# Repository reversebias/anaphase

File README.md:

# anaphase wireless split keyboard

anaphase is a Bluetooth/USB split ergonomic keyboard with a 3D printed case and custom PCB base.

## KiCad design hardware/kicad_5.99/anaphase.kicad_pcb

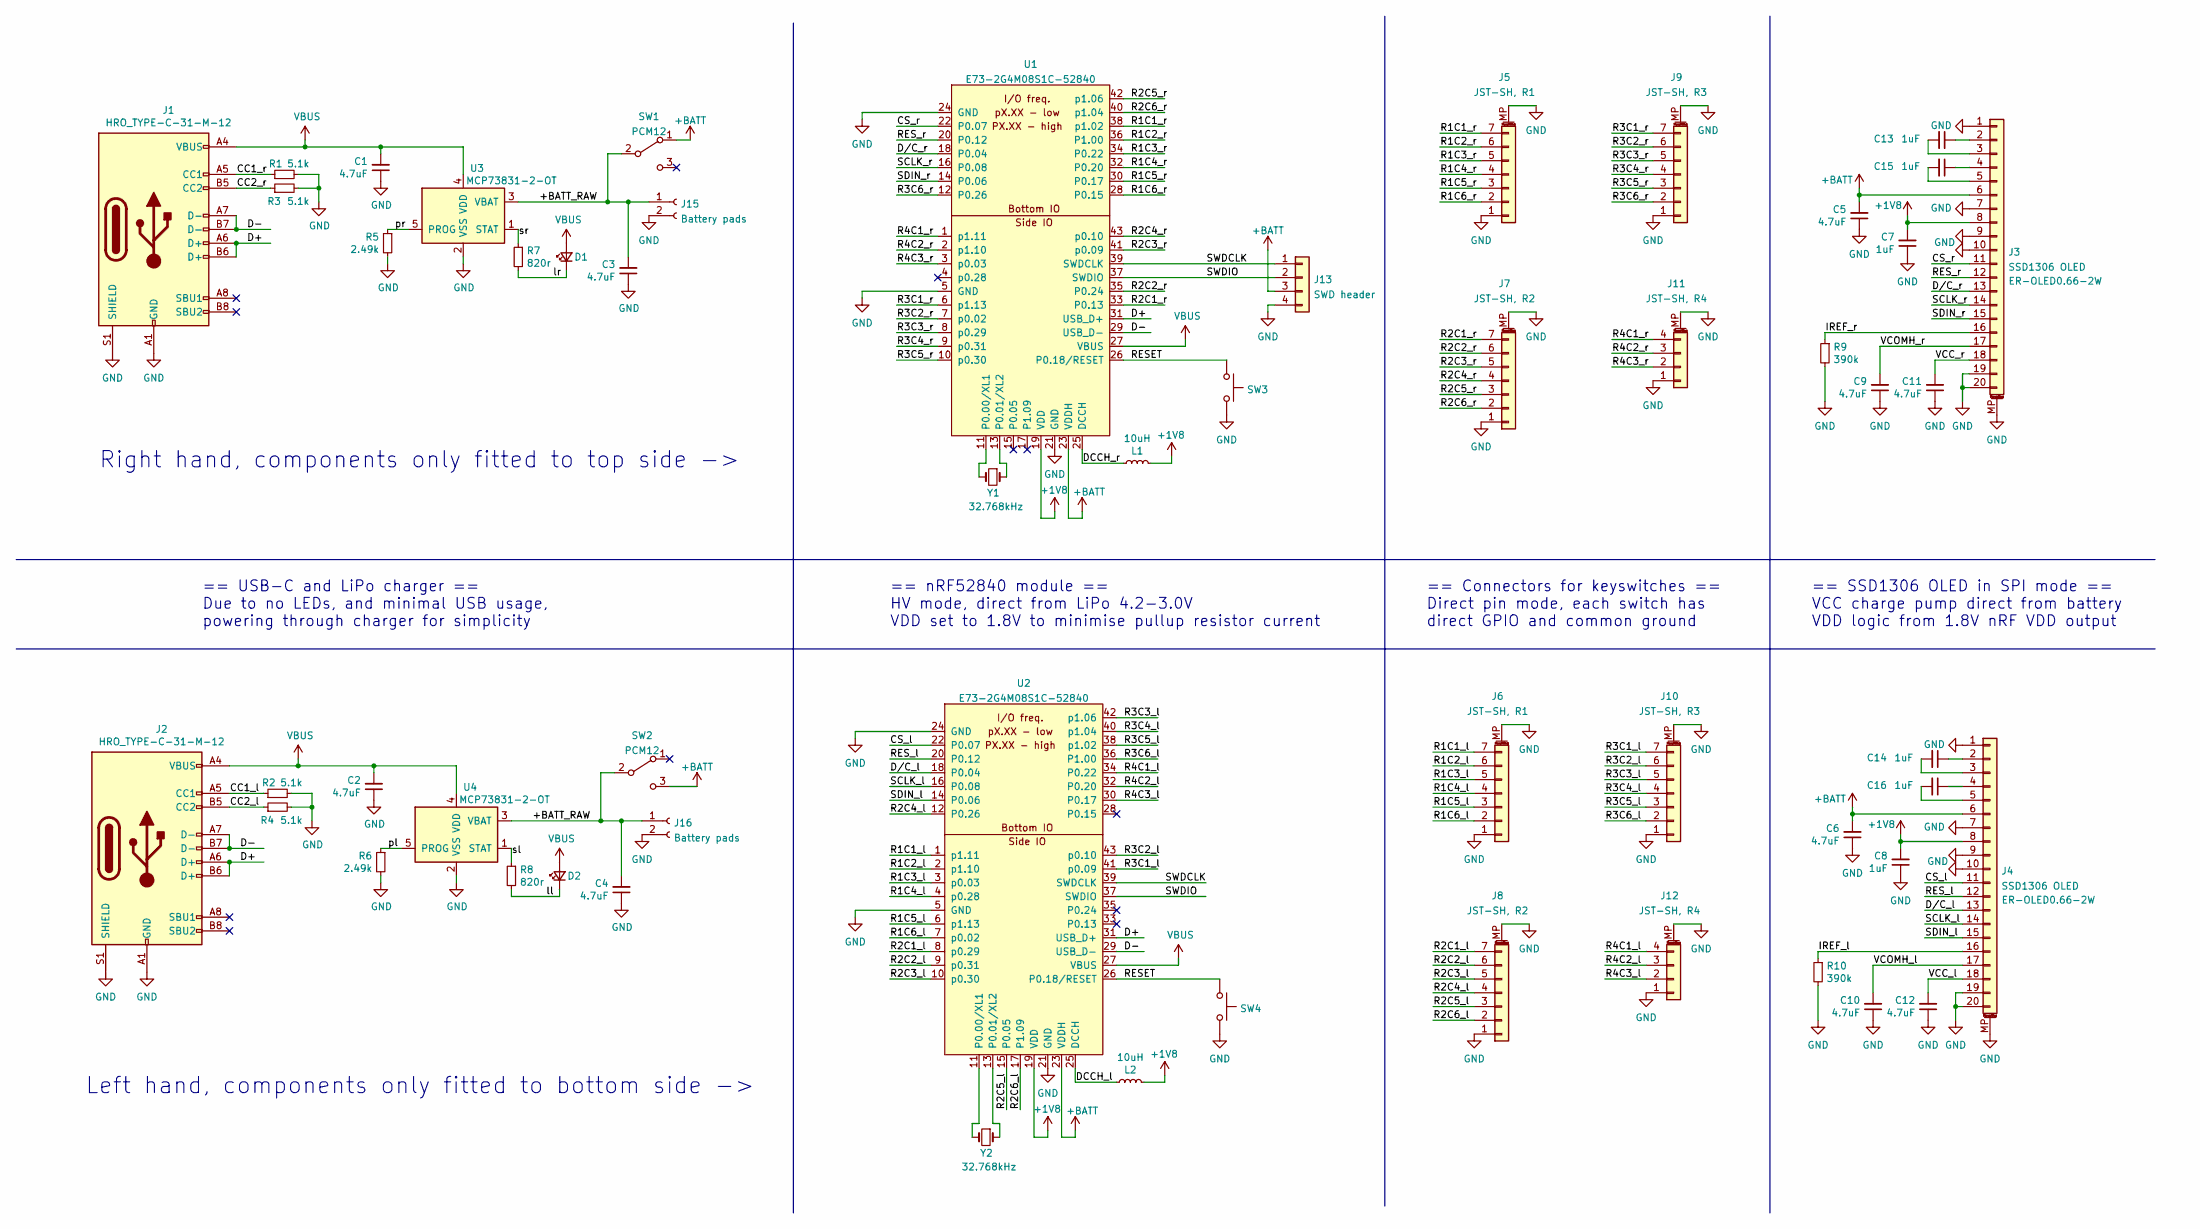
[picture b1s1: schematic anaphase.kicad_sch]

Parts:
C1, C2, C3, C4, C5, C6, C9, C10, C11, C12: 4.7uF; C_0603_1608Metric_Pad1.08x0.95mm_HandSolder
C7, C8, C13, C14, C15, C16: 1uF; C_0603_1608Metric_Pad1.08x0.95mm_HandSolder
D1, D2: AMBER; LED_0603_1608Metric
J1, J2: HRO_TYPE-C-31-M-12; USB_C_Receptacle_HRO_TYPE-C-31-M-12
J3, J4: SSD1306 OLED; Molex_5052782033
J5, J6: JST-SH, R1; JST_SH_BM07B-SRSS-TB_1x07-1MP_P1.00mm_Vertical
J7, J8: JST-SH, R2; JST_SH_BM07B-SRSS-TB_1x07-1MP_P1.00mm_Vertical
J9, J10: JST-SH, R3; JST_SH_BM07B-SRSS-TB_1x07-1MP_P1.00mm_Vertical
J11, J12: JST-SH, R4; JST_SH_BM04B-SRSS-TB_1x04-1MP_P1.00mm_Vertical
J13: SWD header; PinHeader_1x04_P2.54mm_Vertical
J15, J16: Battery pads; L_1210_3225Metric
L1, L2: 10uH; L_0603_1608Metric_Pad1.05x0.95mm_HandSolder
R1, R2, R3, R4: 5.1k; R_0603_1608Metric_Pad0.98x0.95mm_HandSolder
R5, R6: 2.49k; R_0603_1608Metric_Pad0.98x0.95mm_HandSolder
R7, R8: 820r; R_0603_1608Metric_Pad0.98x0.95mm_HandSolder
R9, R10: 390k; R_0603_1608Metric_Pad0.98x0.95mm_HandSolder
SW1, SW2: PCM12; SW_SPDT_PCM12
SW3, SW4: SW_Push; SW_Push_SPST_NO_Alps_SKRK
U1, U2: E73-2G4M08S1C-52840
U3, U4: MCP73831-2-OT; SOT-23-5
Y1, Y2: 32.768kHz; Crystal_SMD_MicroCrystal_CM9V-T1A-2Pin_1.6x1.0mm

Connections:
+1V8: C7.2, C8.2, J3.8, J4.8, L1.2, L2.2, U1.19 (VDD), U2.19 (VDD)
+BATT: C5.2, C6.2, J3.6, J4.6, J13.3, SW1.1 (A), SW2.3 (C), U1.23 (VDDH), U2.23 (VDDH)
/+BATT_RAW: C3.2, C4.2, J15.1, J16.1, SW1.2 (B), SW2.2 (B), U3.3 (VBAT), U4.3 (VBAT)
/CC1_l: J2.A5 (CC1), R2.1
/CC1_r: J1.A5 (CC1), R1.1
/CC2_l: J2.B5 (CC2), R4.1
/CC2_r: J1.B5 (CC2), R3.1
/CS_l: J4.11, U2.22 (P0.07)
/CS_r: J3.11, U1.22 (P0.07)
/D+: J1.A6 (D+), J1.B6 (D+), J2.A6 (D+), J2.B6 (D+), U1.31 (USB_D+), U2.31 (USB_D+)
/D-: J1.A7 (D-), J1.B7 (D-), J2.A7 (D-), J2.B7 (D-), U1.29 (USB_D-), U2.29 (USB_D-)
/DCCH_l: L2.1, U2.25 (DCCH)
/DCCH_r: L1.1, U1.25 (DCCH)
/D/C_l: J4.13, U2.18 (P0.04)
/D/C_r: J3.13, U1.18 (P0.04)
/IREF_l: J4.16, R10.1
/IREF_r: J3.16, R9.1
/R1C1_l: J6.7, U2.1 (p1.11)
/R1C1_r: J5.7, U1.38 (p1.02)
/R1C2_l: J6.6, U2.2 (p1.10)
/R1C2_r: J5.6, U1.36 (P1.00)
/R1C3_l: J6.5, U2.3 (p0.03)
/R1C3_r: J5.5, U1.34 (P0.22)
/R1C4_l: J6.4, U2.4 (p0.28)
/R1C4_r: J5.4, U1.32 (P0.20)
/R1C5_l: J6.3, U2.6 (p1.13)
/R1C5_r: J5.3, U1.30 (P0.17)
/R1C6_l: J6.2, U2.7 (p0.02)
/R1C6_r: J5.2, U1.28 (P0.15)
/R2C1_l: J8.7, U2.8 (p0.29)
/R2C1_r: J7.7, U1.33 (P0.13)
/R2C2_l: J8.6, U2.9 (p0.31)
/R2C2_r: J7.6, U1.35 (P0.24)
/R2C3_l: J8.5, U2.10 (p0.30)
/R2C3_r: J7.5, U1.41 (p0.09)
/R2C4_l: J8.4, U2.12 (P0.26)
/R2C4_r: J7.4, U1.43 (p0.10)
/R2C5_l: J8.3, U2.15 (P0.05)
/R2C5_r: J7.3, U1.42 (p1.06)
/R2C6_l: J8.2, U2.17 (P1.09)
/R2C6_r: J7.2, U1.40 (p1.04)
/R3C1_l: J10.7, U2.41 (p0.09)
/R3C1_r: J9.7, U1.6 (p1.13)
/R3C2_l: J10.6, U2.43 (p0.10)
/R3C2_r: J9.6, U1.7 (p0.02)
/R3C3_l: J10.5, U2.42 (p1.06)
/R3C3_r: J9.5, U1.8 (p0.29)
/R3C4_l: J10.4, U2.40 (p1.04)
/R3C4_r: J9.4, U1.9 (p0.31)
/R3C5_l: J10.3, U2.38 (p1.02)
/R3C5_r: J9.3, U1.10 (p0.30)
/R3C6_l: J10.2, U2.36 (P1.00)
/R3C6_r: J9.2, U1.12 (P0.26)
/R4C1_l: J12.4, U2.34 (P0.22)
/R4C1_r: J11.4, U1.1 (p1.11)
/R4C2_l: J12.3, U2.32 (P0.20)
/R4C2_r: J11.3, U1.2 (p1.10)
/R4C3_l: J12.2, U2.30 (P0.17)
/R4C3_r: J11.2, U1.3 (p0.03)
/RESET: SW3.1, SW4.1, U1.26 (P0.18/RESET), U2.26 (P0.18/RESET)
/RES_l: J4.12, U2.20 (P0.12)
/RES_r: J3.12, U1.20 (P0.12)
/SCLK_l: J4.14, U2.16 (P0.08)
/SCLK_r: J3.14, U1.16 (P0.08)
/SDIN_l: J4.15, U2.14 (P0.06)
/SDIN_r: J3.15, U1.14 (P0.06)
/SWDCLK: J13.1, U1.39 (SWDCLK), U2.39 (SWDCLK)
/SWDIO: J13.2, U1.37 (SWDIO), U2.37 (SWDIO)
/VCC_l: C12.2, J4.18
/VCC_r: C11.2, J3.18
/VCOMH_l: C10.2, J4.17
/VCOMH_r: C9.2, J3.17
/ll: D2.1 (K), R8.2
/lr: D1.1 (K), R7.2
/pl: R6.1, U4.5 (PROG)
/pr: R5.1, U3.5 (PROG)
/sl: R8.1, U4.1 (STAT)
/sr: R7.1, U3.1 (STAT)
GND: C1.1, C2.1, C3.1, C4.1, C5.1, C6.1, C7.1, C8.1, C9.1, C10.1, C11.1, C12.1, J1.A1 (GND), J1.A12 (GND), J1.B1 (GND), J1.B12 (GND), J1.S1 (SHIELD), J2.A1 (GND), J2.A12 (GND), J2.B1 (GND), J2.B12 (GND), J2.S1 (SHIELD), J3.1, J3.7, J3.9, J3.10, J3.19, J3.20, J3.MP (MountPin), J4.1, J4.7, J4.9, J4.10, J4.19, J4.20, J4.MP (MountPin), J5.1, J5.MP (MountPin), J6.1, J6.MP (MountPin), J7.1, J7.MP (MountPin), J8.1, J8.MP (MountPin), J9.1, J9.MP (MountPin), J10.1, J10.MP (MountPin), J11.1, J11.MP (MountPin), J12.1, J12.MP (MountPin), J13.4, J15.2, J16.2, R1.2, R2.2, R3.2, R4.2, R5.2, R6.2, R9.2, R10.2, SW3.2, SW4.2, U1.5 (GND), U1.21 (GND), U1.24 (GND), U2.5 (GND), U2.21 (GND), U2.24 (GND), U3.2 (VSS), U4.2 (VSS)
unnamed: C13.1, J3.2
unnamed: C13.2, J3.3
unnamed: C14.1, J4.2
unnamed: C14.2, J4.3
unnamed: C15.1, J3.4
unnamed: C15.2, J3.5
unnamed: C16.1, J4.4
unnamed: C16.2, J4.5
unnamed: U1.11 (P0.00/XL1), Y1.2
unnamed: U1.13 (P0.01/XL2), Y1.1
unnamed: U2.11 (P0.00/XL1), Y2.2
unnamed: U2.13 (P0.01/XL2), Y2.1
VBUS: C1.2, C2.2, D1.2 (A), D2.2 (A), J1.A4 (VBUS), J1.A9 (VBUS), J1.B4 (VBUS), J1.B9 (VBUS), J2.A4 (VBUS), J2.A9 (VBUS), J2.B4 (VBUS), J2.B9 (VBUS), U1.27 (VBUS), U2.27 (VBUS), U3.4 (VDD), U4.4 (VDD)

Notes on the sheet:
Left hand, components only fitted to bottom side ->
Right hand, components only fitted to top side ->
== USB-C and LiPo charger == Due to no LEDs, and minimal USB usage, powering through charger for simplicity
== nRF52840 module == HV mode, direct from LiPo 4.2-3.0V VDD set to 1.8V to minimise pullup resistor current
== Connectors for keyswitches == Direct pin mode, each switch has direct GPIO and common ground
== SSD1306 OLED in SPI mode == VCC charge pump direct from battery VDD logic from 1.8V nRF VDD output

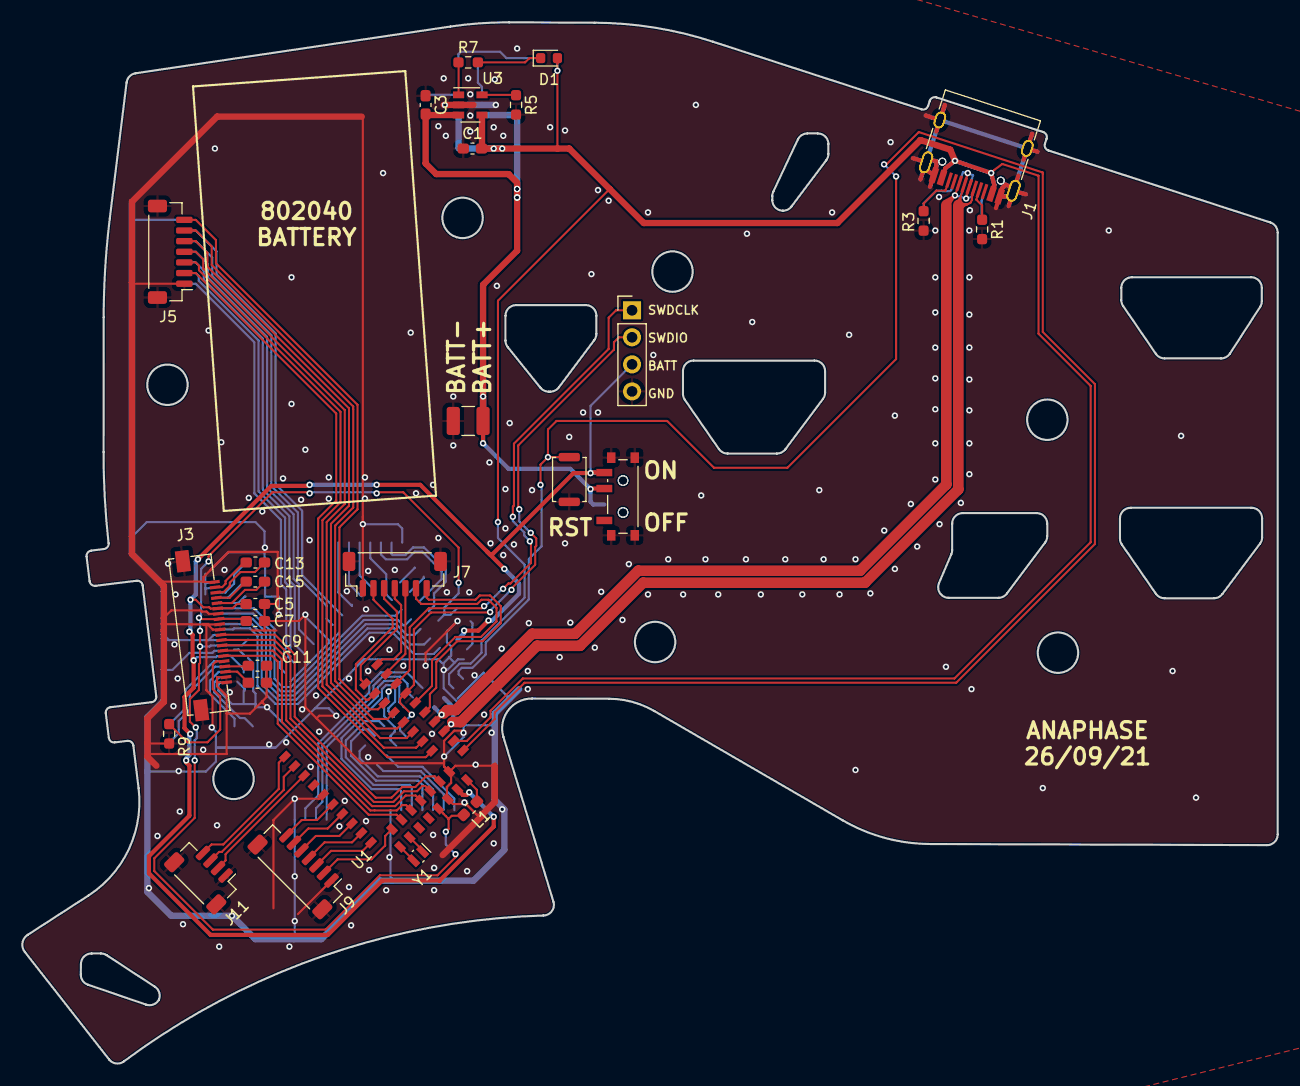
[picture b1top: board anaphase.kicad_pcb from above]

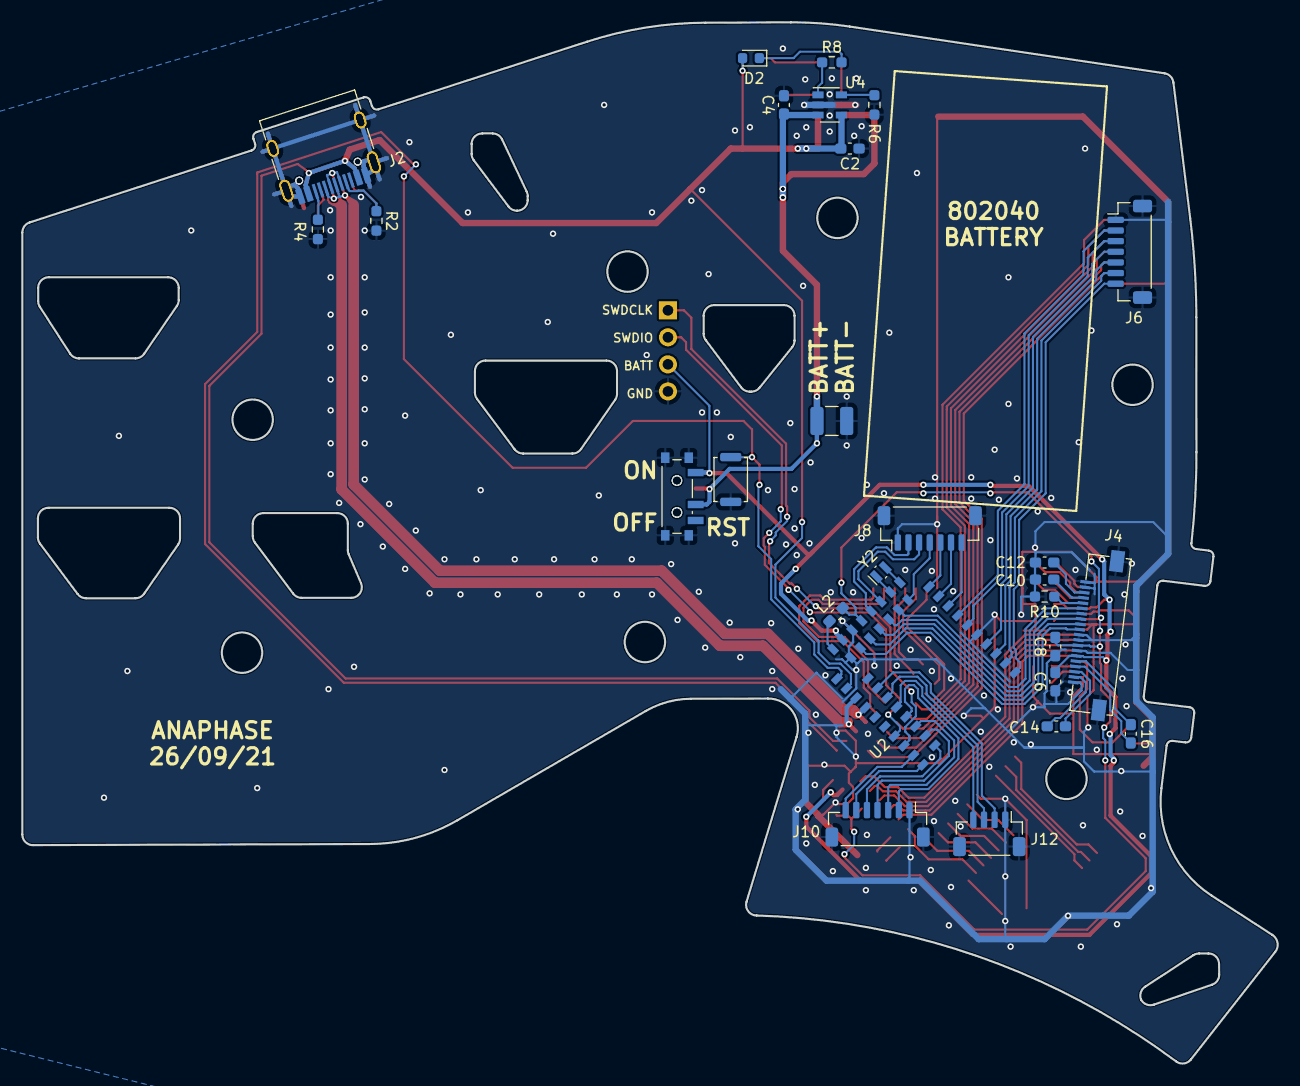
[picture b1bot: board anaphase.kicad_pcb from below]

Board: 2 copper layers, 118.0 x 97.8 mm, 55 parts (27 on the bottom side), 92 nets.

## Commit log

2021-11-01 initial setup of readme
2021-11-01 zmk-config
2021-11-01 non-empty-dir
2021-11-01 numble file structure
2021-11-01 change to split keyboard
2021-11-01 added in fissure files
2021-11-01 new branch for minimal testing
2021-11-01 update for single key
2021-11-01 working spacebar
2021-11-01 oled configured, but no output
2021-11-01 tabs to spaces
2021-11-01 added kconfig
2021-11-01 update based on chat
2021-11-04 working screen, but flipped polarity
2021-11-08 working LCD on single keyboard
2021-11-10 split functionality working
2021-11-13 keymap added
2021-11-13 workspace
2021-11-13 removed old workspace
2021-11-16 Uploading hardware design files
2021-11-22 keymap updates
2021-11-22 sleep timeout 1hr + mute combo
2021-11-22 sleep timeout + mute combo
2021-11-23 basic consumer codes for media
2021-11-23 basic media codes for consumer keys
2022-01-10 broken
2022-01-13 mutex problem with battery level
2022-01-13 maybe solved mutex on battery
2022-01-13 layer status working, but maybe issue with work queue
2022-01-15 layer and battery status, no live updates for battery
2022-01-15 typo
2022-01-16 added debugging messages on every function
2022-01-16 added debugging
2022-01-16 working after memory allocation bug found by pete
2022-01-16 updated to stock listener macro
2022-01-16 WPM status working
2022-01-16 text only oled working, both halves
2022-01-16 remove vscode settings
2022-01-16 turned off debugging for PR
2022-01-16 Update output_status.c
    #ifdef lint
2022-02-10 combos and sleep time updates
2022-03-05 updated debounce times
